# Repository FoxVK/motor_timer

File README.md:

# Motor timer
Timer for controling DC brushed motor on uncontroled aircraft model

## Features:
* Time of thrust can be set in range 5-70s by onboard trimer.
* Thrust can be set in range 0-100% by onboard trimer.
* 5s long ramp of motor turnning off.
* Module shall work with voltage 3.0-5.0V with load up to 3A. (Tested with one Li-Po cell and DC mottor consuming around 1A)

## How to use it:
Set desired time and throttle by trimmers. Turning clockwise means more throttle / longer time.
1) Connect batery.
2) Push the button. At this moment moduler reads values from trimmers, turn on the motor and start count down.
3) Now mottor is running and can be stopped by:
 a) Finishing of count down. (Soft turn off whith ramp down)
 b) Pushing the button. (Turn off wihout any ramp)

Alway power module from accumulator. Do not use laboratory power supply, wall chargers, etc...

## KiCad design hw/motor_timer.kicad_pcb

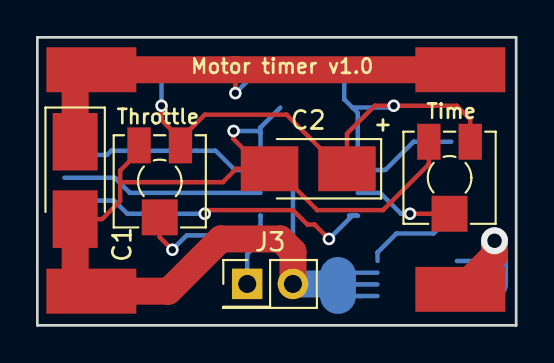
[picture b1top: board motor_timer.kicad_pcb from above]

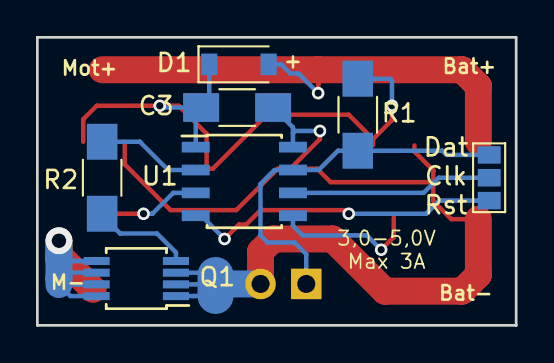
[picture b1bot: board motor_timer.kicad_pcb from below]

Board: 2 copper layers, 26.6 x 16.0 mm, 16 parts (7 on the bottom side), 11 nets.

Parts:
C1: 10uF; CP_Tantalum_Case-B_EIA-3528-21_Hand
C2: 2,2uF; CP_Tantalum_Case-B_EIA-3528-21_Hand
C3: 100n; C_1206_HandSoldering
D1: 1N5819; D_SOD-123
J3: StartBtn; Pin_Header_Straight_2x01_Pitch2.54mm
P1: BAT+; SMT Solder PAD 2.5x5mm
P2: BAT-; SMT Solder PAD 2.5x5mm
P3: MOTOR+; SMT Solder PAD 2.5x5mm
P5: Prog; GS3
Q1: IRF7413; MSOP-8_3x3mm_Pitch0.65mm
R1: 560R; R_1206_HandSoldering
R2: 100R; R_1206_HandSoldering
T1: Throt; Potentiometer_Trimmer_Vishay_TS53YJ
T2: Time; Potentiometer_Trimmer_Vishay_TS53YJ
U1: PIC12F1571-I/P; SOIC-8_3.9x4.9mm_Pitch1.27mm
eP4: MOTOR-; SMT Solder PAD 2.5x5mm

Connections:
+3V3: C2.1, C3.1, D1.1, R1.2, T1.3, T2.3, U1.1
+BATT: C1.1, D1.2, P1.1, P3.1
/M-: Q1.5, Q1.6, Q1.7, Q1.8, eP4.1
/TGate: R2.2, U1.2
/Throt: T1.2, U1.5
/Time: T2.2, U1.3
GND: C1.2, C2.2, C3.2, J3.2, P2.1, Q1.1, Q1.2, Q1.3, T1.1, T2.1, U1.8
unnamed: J3.1, P5.3, R1.1, U1.7
unnamed: P5.1, U1.4
unnamed: P5.2, U1.6
unnamed: Q1.4, R2.1

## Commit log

2017-09-29 Untested version without cut off ramp
2017-10-02 added Release configuration, ramp down on thrust timeout
2017-10-03 Tested ADC, IIR adn PWM, thrust time range changed to 5s-70s. Added Hex file
2017-10-04 Schematic first version
2017-10-05 Changed transistor. Assigned packages to parts.
2017-10-05 Routed PCB with routes on wrong layers
2017-10-07 A bit broken small PCB
2017-10-07 Final version of small PCB. But there are broken referneces betveen schamatic and board.
2017-10-07 update of resources
2017-10-09 Created project lib with smaller solder pad.
2017-10-09 XS PCB
    Fixed references between schm and pcb
2017-11-12 V1.0
2017-11-12 Version 1.0 - Fixed bad reading of push button - Ramp down changed to be longer 5s instead of 2s - Added few comments
